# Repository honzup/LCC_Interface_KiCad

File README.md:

# LCC / CAN interface board – Rev C

A small two-layer board that connects any 3.3 V microcontroller with a CAN
controller (ESP32 TWAI, STM32, …) to an **LCC / OpenLCB** bus using standard
RJ45 cables. Designed in KiCad for model railway layouts; in daily use on my
layout under every LCC node and the Ethernet bridge
([lcc-eth-bridge](https://github.com/honzup/lcc-eth-bridge)).

Why a dedicated board rather than a ready-made transceiver module:

- **RJ45 in and out** – robust connectors and ordinary straight-through patch
  leads; the bus daisy-chains through the board, so unplugging the processor
  doesn't break the bus.
- **Termination by jumper** – fit JP1 only on the boards at the two ends of the
  bus. (Many ready-made SN65HVD230 modules have a 120 Ω resistor soldered on
  permanently.)
- **Test points and LEDs** – probe pads for CAN_H, CAN_L, CAN_GND, 3V3, TX and
  RX, plus power / TX / RX LEDs: you can see at a glance whether the board has
  power, whether the node transmits and whether it hears the bus.
- **ESD protection** on the bus lines (PESD1CAN TVS diode), shields tied to
  CAN ground.
- **TCAN33x footprint** – built with a TCAN332; also takes the TCAN330/334/337.

## Specification

- Transceiver U1: TI **TCAN332DR**, 3.3 V, SOIC-8. LCC's 125 kbit/s is far inside
  its rating.
- J1/J2: Amphenol **RJHSE-5380** shielded RJ45, **no magnetics**. Do not
  substitute an Ethernet MagJack – its transformers block CAN. Not the
  `-5385` (LED) variant either.
- J3: 4-pin 2.54 mm header to the microcontroller: **1 GND, 2 3V3, 3 TX, 4 RX**.
  The board is powered from the microcontroller's 3.3 V – wire GND and 3V3,
  not just TX/RX.
- All eight RJ45 conductors pass straight through J1 ↔ J2. Bus power (pins 7/8)
  is pass-through only and is not connected to the board's supply.
  Non-isolated design.
- 60 × 50 mm, two layers, 1.6 mm, solid CAN_GND pour on the bottom.
  Four M3 mounting holes, 4 mm in from each corner (52 × 42 mm pattern).

### RJ45 pinout (LCC standard S-9.7.1.1)

| Pin | Signal | T568B colour |
|-----|--------|--------------|
| 1 | CAN_H | white/orange |
| 2 | CAN_L | orange |
| 3 | CAN_GND | white/green |
| 4 | ALT_L (pass-through) | blue |
| 5 | ALT_H (pass-through) | white/blue |
| 6 | CAN_GND | green |
| 7 | PWR_NEG (pass-through) | white/brown |
| 8 | PWR_POS (pass-through) | brown |
| shell | CAN_GND | |

CAN_H/CAN_L share one twisted pair, so ordinary **straight-through** Cat5e/Cat6
patch leads work. Never use crossover or flat (untwisted) cable.

## Ordering and assembly

- **PCB:** upload `LCC_Interface_RevC_gerbers.zip` to any fab (JLCPCB, PCBWay …):
  2 layers, 1.6 mm, default settings.
- **Parts:** `BOM.csv` (with Digi-Key part numbers) and `digikey-order.txt`
  (paste into Digi-Key's quick order). `bom/ibom.html` is an interactive BOM –
  open it in a browser while soldering to highlight each part's position.
- **Hand soldering:** all SMD parts are 0805 or SOIC-8/SOT-23 with hand-solder
  pads. R2/R3 are **not fitted** for the TCAN332 – fit them only for a
  TCAN330/334/337, where they hold the mode pins low.
- **Reflow all eight U1 pins.** Cold joints on hand-soldered SOIC-8s tend to
  come in groups; if a fresh board misbehaves, reflow the whole chip rather
  than chasing one pin at a time.
- **LED colours:** the LEDs run from 3.3 V through 1 kΩ. Use red, orange,
  yellow or standard green (≈2 V forward voltage). Blue, white and "true" green
  (≈3 V) are barely visible at this current.

## Bring-up checks

With the board powered and connected to the bus:

| Check | Expect |
|-------|--------|
| PWR LED | on |
| 3V3 test point (TP4) | 3.3 V |
| CAN_H and CAN_L to CAN_GND, bus idle | both ≈ 1.9 V – normal for a 3.3 V transceiver, not the 2.5 V of 5 V parts |
| TX / RX test points, bus idle | ≈ 3.3 V (high = recessive) |
| RX LED | flickers on any bus traffic |
| TX LED | flickers only when *this* node transmits |
| CAN_H ↔ CAN_L, everything powered off | ≈ 60 Ω with both ends terminated; ≈ 120 Ω means only one end |

RX flickering with TX dark means the node hears the bus but isn't transmitting
– check the TX wire and the node firmware.

## Files

| File | What |
|------|------|
| `LCC_Interface.kicad_pro` / `.kicad_sch` / `.kicad_pcb` | KiCad project (made in KiCad 10; the schematic is the source of truth) |
| `LCC_Interface_RevC_gerbers.zip` (+ unzipped folder) | Gerbers and drill files for ordering |
| `BOM.csv`, `digikey-order.txt`, `bom/ibom.html` | Bill of materials, Digi-Key order, interactive BOM |
| `images/` | Renders |

## Revision history

- **Rev C** (current) – adds power / TX / RX LEDs and test points for 3V3, TX
  and RX. No circuit change. Tag `rev-c`.
- **Rev B** – first manufactured version. Common ground between the board and
  the bus, PESD1CAN ESD protection, 4.7 µF bulk capacitor, shielded RJ45s,
  TCAN33x-family footprint. Tag `rev-b`.
- **Rev A** – an AI-drafted schematic whose net labels had landed on the wrong
  pins (TX/RX and CAN_H/CAN_L swapped, RJ45 pinout mirrored) – a reminder to
  check every pin against the datasheets.

## Licence

CERN Open Hardware Licence v2 – Permissive (CERN-OHL-P-2.0) – see `LICENSE`.

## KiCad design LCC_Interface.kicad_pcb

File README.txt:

Universal LCC / CAN Interface  -  Rev C
=======================================

Open LCC_Interface.kicad_pro in KiCad 9 or 10.
The project contains a native .kicad_sch and .kicad_pcb.

The schematic is the authoritative source and passes ERC with 0 errors
(remaining warnings are cosmetic: off-grid endpoints, and the embedded "LCC"
symbol library not being registered in a sym-lib-table - both harmless).

WHAT CHANGED FROM REV B
-----------------------
Rev C adds passive diagnostic indicators only (no new ICs, no net-logic change):

1. POWER LED. D2 (0805 LED) + R4 (1k): +3V3 -> R4 -> D2 anode -> D2 cathode ->
   CAN_GND. Lit whenever the board's 3V3 rail is present. Placed next to U1 so
   the +3V3 tap sits at the transceiver VCC pad.
2. TX ACTIVITY LED. D3 + R5 (1k): +3V3 -> R5 -> D3 anode; D3 cathode -> CAN_TX.
   TXD idles high (recessive) so the LED is dark at idle and blinks on transmit.
3. RX ACTIVITY LED. D4 + R6 (1k): +3V3 -> R6 -> D4 anode; D4 cathode -> CAN_RX.
4. PROBE PADS. TP4/TP5/TP6 added (board-only, same THT pad style as TP1-3) on
   +3V3 / CAN_TX / CAN_RX respectively.

The 1k series resistors are deliberate - they hold LED current to ~1-2 mA so the
indicators load the 3V3 rail and the TX/RX lines only lightly. Board is still the
same 60 x 50 mm two-layer outline with the solid CAN_GND bottom pour; DRC clean
(0 violations, 0 unconnected, fully routed).

WHAT CHANGED FROM REV A (ChatGPT draft)
---------------------------------------
The Rev A schematic and PCB disagreed. The PCB net assignment was correct, but
the schematic had a systematic Y-axis flip: almost every net label sat on the
WRONG pin (TXD<->RXD swapped, CANH<->CANL swapped, the whole RJ45 pinout
mirrored, MCU header reversed) and the transceiver ground was never tied to the
bus CAN_GND. Rev B fixes the schematic so it matches the (correct) board intent,
and adds the "universal" features:

1. GROUND FIX. Local ground (U1 pin 2, MCU GND) is now one net with the bus
   CAN_GND (RJ45 pins 3 & 6) and the connector shells. This is mandatory on a
   non-isolated CAN tap.
2. UNIVERSAL FAMILY SUPPORT. Pins 5 and 8 of the SOIC-8 now go to DNP 10k
   pulldowns R2/R3. TCAN332 = both pins NC (leave R2/R3 unfitted). Fit R2/R3
   to drop in a TCAN330 (SHDN/S), TCAN334 (SHDN/STB) or TCAN337 (FAULT/S) -
   the pulldowns hold their mode pins low = normal/active operation.
3. BUS ESD PROTECTION. D1 = PESD1CAN CAN-bus TVS (SOT-23) across CAN_H/CAN_L,
   referenced to CAN_GND.
4. BULK CAP. C2 (4.7uF) added at VCC alongside C1 (100nF).
5. CONNECTOR. J1/J2 changed to the shielded Amphenol RJHSE-5380 (vetted KiCad
   library footprint, NO magnetics - correct for LCC). Metal shell pads (SH)
   are on CAN_GND. Do NOT substitute an Ethernet magjack (those have
   transformers and will not pass CAN).

ELECTRICAL
----------
- U1 TCAN332DR, 3.3 V (pins 5 & 8 = NC on the 332)
- J1/J2 dual LCC RJ45, all 8 conductors daisy-chained J1<->J2 (bus pass-through)
- J3 four-pin MCU header: 1 GND, 2 3V3, 3 CAN_TX (->TXD), 4 CAN_RX (<-RXD)
- Board is powered from the MCU 3V3 rail; bus power (PWR_POS/PWR_NEG) is
  pass-through only and is kept separate from CAN_GND. Non-isolated design.
- R1 120R termination, in series with JP1. Fit JP1 ONLY on the two boards at the
  physical ends of the bus.
- LCC = 125 kbit/s (well within the TCAN332's 1 Mbit/s rating).

LCC RJ45 pin assignment (OpenLCB S-9.6.1):
  1 CAN_H
  2 CAN_L
  3 CAN_GND
  4 ALT_L   (reserved, pass-through)
  5 ALT_H   (reserved, pass-through)
  6 CAN_GND
  7 PWR_NEG
  8 PWR_POS
  Shell/shield -> CAN_GND

PCB - COMPLETE
--------------
The Rev A board was regenerated from scratch to match the corrected schematic:
all 27 footprints placed (Rev C added D2-D4, R4-R6, TP4-6), nets assigned, and every signal autorouted
(Freerouting) on a 60 x 50 mm two-layer board (well under the 100 x 100 mm
budget-fab price break). The bottom layer is a solid CAN_GND ground pour; every
ground and shield pad connects to it. Four M3 mounting holes, 4 mm in from each
corner (52 x 42 mm hole pattern).

Verified with KiCad's design-rule check:
   DRC violations:      0
   Unconnected items:   0   (fully routed)
   Net names match the schematic.

Remaining DRC "schematic parity" notes are cosmetic only: empty Datasheet
metadata fields, and TP1-6 / H1-H2 being board-only (test points + mounting
holes are intentionally not in the schematic).

BEFORE ORDERING, check these mechanical points in the GUI:
1. RJ45 orientation - confirm each socket's cable opening faces off the board
   edge so cables can plug in. Rotate a connector 180 deg if it faces inward.
2. Confirm the Amphenol RJHSE-5380 footprint matches your exact ordered part
   (-5380 plain vs -5385 with LEDs).
3. Component placement is functional but not optimised for looks - nudge parts
   if you want, then re-run DRC (Inspect -> Design Rules Checker).

board_top.png is a 3D render of the finished board.
LCC_Interface.kicad_pcb.revA-bak is the original ChatGPT board, kept as a backup.

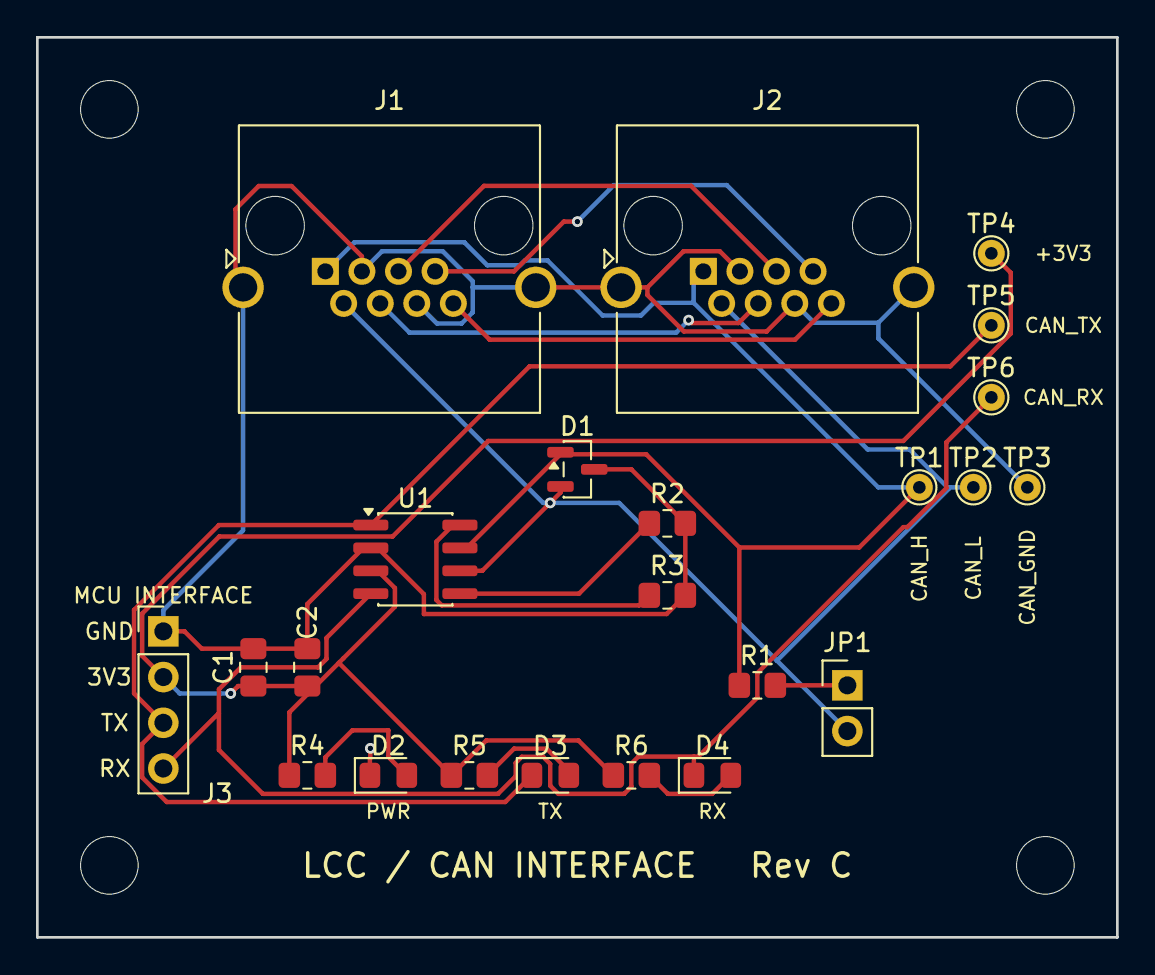
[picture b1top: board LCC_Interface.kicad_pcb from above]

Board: 2 copper layers, 60.0 x 50.0 mm, 27 parts (0 on the bottom side), 16 nets.

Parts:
C1: 100nF; C_0805_2012Metric_Pad1.18x1.45mm_HandSolder
C2: 4.7uF; C_0805_2012Metric_Pad1.18x1.45mm_HandSolder
D1: PESD1CAN; SOT-23
D2, D3, D4: LED; LED_0805_2012Metric_Pad1.15x1.40mm_HandSolder
H1, H2, H3, H4: MountingHole_3.2mm_M3
J1, J2: LCC RJ45; RJ45_Amphenol_RJHSE5380
J3: MCU INTERFACE; PinHeader_1x04_P2.54mm_Vertical
JP1: TERM ENABLE; PinHeader_1x02_P2.54mm_Vertical
R1: 120R; R_0805_2012Metric_Pad1.20x1.40mm_HandSolder
R2, R3: 10k DNP; R_0805_2012Metric_Pad1.20x1.40mm_HandSolder
R4, R5, R6: 1k; R_0805_2012Metric_Pad1.20x1.40mm_HandSolder
TP1, TP2, TP3, TP4, TP5, TP6: TP; TestPoint_THTPad_D1.5mm_Drill0.7mm
U1: TCAN332DR; SOIC-8_3.9x4.9mm_P1.27mm

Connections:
/+3V3: C1.1, C2.1, J3.2, R4.1, R5.1, R6.1, TP4.1, U1.3
/ALT_H: J1.5, J2.5
/ALT_L: J1.4, J2.4
/CAN_GND: C1.2, C2.2, D1.3, D2.1, J1.3, J1.6, J1.SH, J2.3, J2.6, J2.SH, J3.1, R2.2, R3.2, TP3.1, U1.2
/CAN_H: D1.1, J1.1, J2.1, R1.1, TP1.1, U1.7
/CAN_L: D1.2, J1.2, J2.2, JP1.2, TP2.1, U1.6
/CAN_RX: D4.1, J3.4, TP6.1, U1.4
/CAN_TX: D3.1, J3.3, TP5.1, U1.1
/LED_PWR: D2.2, R4.2
/LED_RX: D4.2, R6.2
/LED_TX: D3.2, R5.2
/MODE5: R2.1, U1.5
/MODE8: R3.1, U1.8
/PWR_NEG: J1.7, J2.7
/PWR_POS: J1.8, J2.8
/TERM_MID: JP1.1, R1.2
